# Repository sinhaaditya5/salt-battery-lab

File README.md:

<div align="center">

<br>

**A rebuildable engineering and business study of a sodium "salt battery" startup:<br>
from DFT and cell models to CAD, PCB, techno-economics and an honest go/no-go verdict.**

[Quickstart](#quickstart) ·
[Results](#results-at-a-glance) ·
[Gallery](#gallery) ·
[Architecture](#architecture) ·
[Verdict](#the-verdict) ·
[Deliverables](DELIVERABLES) ·
[Release v1.1.0](https://github.com/sinhaaditya5/salt-battery-lab/releases/tag/v1.1.0)

</div>

---

> [!IMPORTANT]
> **This is a pre-prototype study, not a product.** No cell has been built, so nothing here is measured.
> Every number carries an evidence tag (`[LIT]`, `[VENDOR]`, `[CALC]`, `[SIM]`, `[ASSUMPTION]`, `[TARGET]`) that
> resolves in [`CLAIMS_LEDGER.csv`](CLAIMS_LEDGER.csv). The designs are concepts, **not for fabrication**.
> See the [claims boundary](#claims-boundary).

## Overview

**Salt Battery Lab** answers two startup briefs with one parameter set, one claims ledger and one rebuild script:

| | What it is | Highlights |
|---|---|---|
| 💧 **[Aqueous track](DELIVERABLES)** · `sim/s01…s10` | **R0/R1**: a water-based sodium-ion battery as *"the battery you're allowed to put indoors"* for data-centre and telecom UPS in India. The study runs from a kit re-run to PyBaMM validation, an R1 DFN with Monte Carlo, gas and water budgets, a uMLIP + DFT+U screen, build-up, thermal/abuse, TEA and market sizing. | 10 simulations · 164 logged sources · 28-slide deck · report · YC W27 application · **no-go memo** |
| 🧂 **[Project Salt](PROJECT_SALT)** · `sim/s11…s16` | **Salt-derived chemistries** tested against 360 Wh/kg, a 5-minute charge for 1,500 km, $3 and non-flammability. Includes a 30-architecture feasibility matrix, DFT+U on Na/NaCl/Cl₂/Fe-Co-Ni chlorides, a salt-iron cell model, factory scenarios, the S-cell R0, the SCM-1 board and firmware, and the P1 / SM-48T / SC-UPS-1 designs. | QE 7.6 on AWS spot · STEP + CADCraft drawings · KiCad 10 · 19/19 firmware tests · **Outcome B** |

<div align="center">

<br><sub><b>SM-48T</b>: 48 V telecom/edge backup module concept (7U, 19-inch) built from P1 planar salt-iron cells. Blender render of the build123d CAD model.</sub>
</div>

## Results at a glance

Every number below is regenerated by [`run_all.sh`](run_all.sh) and traces to a claim in [`CLAIMS_LEDGER.csv`](CLAIMS_LEDGER.csv)
or [`PROJECT_SALT/00_START_HERE/CLAIMS_LEDGER.csv`](PROJECT_SALT/00_START_HERE/CLAIMS_LEDGER.csv).

| ID | Area | Test | Result | Status |
|:--:|---|---|---|:--:|
| T1 | Software | pytest suites on the EC2 build host | 80 collected: 78 passed, 2 skipped, 0 failed | ✅ pass |
| T2 | Reproducibility | S1 re-run of the R0 kit scripts vs the kit's expected outputs | 9 / 9 match `[C-101]` | ✅ pass |
| T3 | Cell model | S2 PyBaMM sodium DFN vs published curves (gate: MAE ≤ 60 mV) | misses by **67–121 mV** `[SIM; C-102]` | ❌ fail, documented |
| T4 | Atomistic | S5 uMLIP voltages and birnessite interlayer vs literature | voltage MAE 0.33 V (0.7 V errors for NTP and Prussian white); interlayer 7.16 Å vs 7.19 Å XRD `[SIM; C-110, C-111]` | 🔶 finding |
| T5 | DFT | S11 PBE conversion voltages, 2 Na + MCl₂ → 2 NaCl + M | Fe 2.60 V, Ni 2.85 V vs 2.49, 2.68 V experiment; Fe/Co/Ni errors +0.11 to +0.27 V at U = 0 `[SIMULATED]` | ✅ pass |
| T6 | Cell design | S7 R1 12 V block energy density | **17.6 Wh/kg** (13.7–22.1), Aquion-class `[CALC; C-115]` | 🔶 finding |
| T7 | Thermal | S8 temperature rise in a 15-min UPS discharge | 2.8 K `[SIM; C-119]` | ✅ pass |
| T8 | Cost | S9 R1 cost vs LFP pack price | **~$350/kWh** `[CALC; C-122]` vs $70/kWh `[LIT; C-005]` | 🔶 finding |
| T9 | TCO | S9 15-year cost per kWh of 15-min UPS backup | R1 $1,228 · LFP $720 · VRLA $990 `[CALC; C-123]` | 🔶 finding |
| T10 | Energy | S12 best salt-derived cell (N08) vs the 360 Wh/kg target | P50 **259**, P90 292 Wh/kg `[CALCULATED]` | ❌ target missed |
| T11 | Charging | S13 5-min charge for 1,500 km | needs **3.8 MW** (11.7C) vs the 3.75 MW MCS ceiling `[CALCULATED]` | ❌ target missed |
| T12 | Cost floor | S12/S13 $3 target, six readings | inactive parts alone exceed $3/kWh; cell floors $41–152/kWh `[CALCULATED]` | ❌ target missed |
| T13 | Salt-iron cell | S14 5-min charge of the Na–FeCl₂ cell | 0.8–4.3 V overpotential drives it past the 3.05 V overcharge reaction `[SIMULATED]` | ❌ target missed |
| T14 | Factory | S15 1 GWh/yr India, salt-iron vs NFPP | ~$380/kWh vs ~$83/kWh `[CALCULATED]` | 🔶 finding |
| T15 | Electronics | SCM-1 ERC and firmware host tests | ERC 0 · 19 / 19 tests; layout is a draft (37 unrouted nets) | 🔁 in progress |
| T16 | Documents | Claims linter over the deck, report and one-pager | 0 problems | ✅ pass |

<sub>✅ pass · ❌ fails a founder target or a validation gate, recorded rather than hidden · 🔶 finding that reshapes the plan · 🔁 in progress</sub>

**What the simulations changed:** energy density sets the cost. The R1 block lands at 17.6 Wh/kg, where Aquion sat before it failed, and at ~$350/kWh, so the aqueous *factory* company is a **no-go** (T6, T8). Fire codes don't hand the advantage to aqueous sodium either: an unlisted chemistry gets 3 kWh under IFC 2024, against lithium's 20 kWh `[LIT; C-007, C-008]`.

Project Salt showed the founder targets conflict with physics and economics (T10–T13). **The salt is almost free; the battery is not.** The one testable lever is a ≤ 0.5 mm β''-alumina separator with a ≥ 75 mAh/cm² salt-iron cathode `[CALCULATED]`. The S-cell R0 build package exists to test exactly that, after a near-free buyer test.

## Gallery

### Devices

| R1 12 V monobloc | R1 exploded, annotated | R1 UPS cabinet in a data-centre room |
|:--:|:--:|:--:|
|  |  |  |
| **SM-48T 48 V module** | **SM-48T cutaway** | **SC-UPS-1 cabinet, open** |
|  |  |  |
| **P1 planar salt-iron cell, exploded** | **S-cell R0 test cell** | **SCM-1 salt-cell test monitor** (draft layout) |
|  |  |  |

<div align="center">

<br><sub><b>SB-GA-001</b>: R1 12 V monobloc general arrangement (front, top and side views, section A-A, vent detail B) at 1:2 on A2, generated headlessly in CADCraft (<a href="drawings/out/SB-GA-001.pdf">PDF</a> · <a href="drawings/out/SB-GA-001.dxf">DXF</a>). Concept only.</sub>
</div>

<details>
<summary><b>More drawings:</b> SB-SM-001 (SM-48T module)</summary>

Also in [`drawings/out`](drawings/out):
- SB-GA-002: R1 cell and electrode stack
- SB-GA-003: R1 UPS cabinet
- SB-SC-001: S-cell R0
- SB-TM-001: module thermal management
- SB-UPS-001: SC-UPS-1

</details>

### Simulations

| Chemistry matrix: Pareto front (S12) | Energy ladder vs the 360 Wh/kg target (S12) |
|:--:|:--:|
|  |  |
| **DFT+U: conversion voltage vs U (S11)** | **DFT+U: projected density of states (S11)** |
|  |  |
| **Fast charge: validated Li-ion DFN benchmark (S13a)** | **Six readings of the $3 target (S13b)** |
|  |  |
| **Salt-iron cell model (S14)** | **Factory cost and tornado (S15)** |
|  |  |
| **uMLIP voltage parity (S5)** | **R1 rate retention vs electrode loading (S3)** |
|  |  |
| **R1 cost waterfall (S9)** | **15-year UPS TCO: R1 vs LFP vs VRLA (S9)** |
|  |  |

<details>
<summary><b>More charts:</b> PyBaMM validation, water window, thermal, build-up, market</summary>

| PyBaMM validation, documented failure (S2) | Water stability window (S4) |
|:--:|:--:|
|  |  |
| **R1 temperature in a 15-min UPS discharge (S8)** | **SM-48T module thermal budget (S16)** |
|  |  |
| **Energy density vs benchmarks (S7)** | **India UPS market, TAM / SAM / SOM (S10)** |
|  |  |

Every chart also exists as a 300 dpi PNG and an SVG, with a `.caption.txt` file that carries its claim tags ([`DELIVERABLES/7_simulation_charts`](DELIVERABLES/7_simulation_charts)).

</details>

### System design

| System architecture | Salt-iron cell electrochemistry |
|:--:|:--:|
|  |  |
| **SM-48T module electrical** | **Safety comparison** |
|  |  |
| **Validation ladder (aqueous)** | **Gate ladder G1–G5 (S-cell)** |
|  |  |

<details>
<summary><b>Roadmap and unit economics</b></summary>

</details>

## Architecture

Every tagged value flows from **one package**, [`params/`](params): `product_params.py` holds the tagged values and `design.py` derives geometry, mass and energy from them. The CAD, the drawings, the firmware limits, the spreadsheets and every simulation therefore describe the same product. Every claim in a document resolves to the ledger.

```mermaid
flowchart LR
    P["params/*.py<br/><i>single source of truth</i>"]
    L["CLAIMS_LEDGER.csv<br/><i>every number → evidence</i>"]
    R["research/<br/>sources.csv · notes"]

    subgraph SIM [Simulations]
        A[s05 uMLIP · s06/s11 DFT+U<br/>QE 7.6 on EC2 spot]
        C[s02 PyBaMM · s03 DFN+MC<br/>s04 gas · s08/s16 thermal · s14 S-cell]
        E[s07 build-up · s09 TEA · s10 market<br/>s12 matrix · s13 targets · s15 factory]
    end
    subgraph GEO [Geometry and hardware]
        CAD[cad/ build123d → STEP/STL/GLB]
        DWG[drawings/ CADCraft → DXF/PDF]
        PCB[pcb/ KiCad + firmware limits.h]
    end
    subgraph OUT [Communication]
        RND[renders/ Blender]
        DOC[docs/ deck · report · one-pager]
        FIN[finance/ live-formula xlsx]
        VID[video/ narrated explainer]
    end
    T["tests/ + docs/lint.py"]
    PK["DELIVERABLES/ · PROJECT_SALT/"]

    P --> SIM
    P --> CAD --> RND
    P --> DWG
    P --> PCB
    R --> L
    SIM --> L
    SIM --> FIN
    L --> DOC
    SIM & CAD & PCB & DOC & FIN & VID --> PK
    T -. gates .-> P & SIM & CAD & DOC
```

More detail in [`docs/ARCHITECTURE.md`](docs/ARCHITECTURE.md).

## Quickstart

```bash
git clone https://github.com/sinhaaditya5/salt-battery-lab.git
cd salt-battery-lab

make setup          # Python 3.12 venv + pinned CI requirements
make link           # expose the clone at the lab path the scripts expect
make check          # integrity gate: secrets, file sizes, JSON/CSV/Python validity
make test           # params · sim models · DFT · docs lint · Project Salt suites
make firmware-test  # SCM-1 firmware host unit tests (C11, -Werror)
```

Use the parameter set directly:

```python
from params.product_params import MONOBLOC, R0, ALLOWED_TAGS   # tagged values
import params.design as D                                      # derived geometry, mass, energy
from params.scell_params import OPERATE                        # S-cell operating window → firmware limits
```

### Full pipeline

`./run_all.sh` rebuilds every artefact in dependency order and never launches cloud machines. Stages beyond the models need external tools:

| Stage | Command | Requires |
|---|---|---|
| Integrity, tests | `make check` · `make test` · `make firmware-test` | Python 3.12, a C compiler |
| Models (S1–S16) | `./run_all.sh --fast` | `tools/ec2_build/requirements.txt` (PyBaMM, MACE, CHGNet, pymatgen, ASE) |
| ML potentials | `scripts/fetch_assets.sh models` | MACE-MP-0 / 0b3 weights (SHA-256 pinned) |
| CAD | `python cad/make_cad.py` · `make_scell.py` · `make_smodule.py` | build123d (OpenCascade) |
| Drawings | `python drawings/make_drawings.py` | CADCraft `cadcraft-cli` |
| Renders | `python renders/run_renders.py` · `run_salt_renders.py` | Blender 5.0.1 |
| PCB | `pcb/build_scm.sh` | KiCad 10 (`kicad-cli`); Freerouting optional |
| Spreadsheets, docs | `python finance/make_*.py` · `python docs/make_*.py` | LibreOffice (recalculation check) |
| MATLAB stems | `python tools/matlab/make_stem.py --run` | GNU Octave |
| Video | `python video/make_video.py` | ffmpeg, macOS `say` |
| README imagery | `make assets` | Pillow, ffmpeg |
| DFT (opt-in, costs money) | `sim/s06_dft_ec2/launch.sh` → `sim/s11_dft_chlorides/ec2/ec2_s11.sh` | AWS account, QE 7.6, founder approval |

Step-by-step instructions are in [`docs/REPRODUCIBILITY.md`](docs/REPRODUCIBILITY.md). Heavy builds ran on an x86 spot build host ([`tools/ec2_build/`](tools/ec2_build)).

## The verdict

Each version added one layer to the study:

| Version | Layer | Key documents |
|---|---|---|
| v0.1 | Lab layout, verified R0 kit (50/50 SHA-256), S1 kit re-run, S5 uMLIP relax, S6 DFT+U package, params v0 | [R0 kit](00_source_kit/Salt_Battery_R0_Reference_Cell_Kit_v1/START_HERE.md) · [S6](sim/s06_dft_ec2/README.md) |
| v0.2 | S2–S4 and S8 cell models; R1 design; 164 sources; S9 TEA; S7 build-up; S10 market; IDEA v2 with kill criteria | [IDEA v2](decisions/IDEA_v2.md) · [research notes](research/RESEARCH_NOTES.md) |
| v0.3 | Diagrams, claims ledger, decision memo, test suites, claims linter, financial model, 28-slide deck | [decision memo](DELIVERABLES/STARTUP_DECISION_MEMO.md) · [red team](decisions/RED_TEAM.md) |
| v0.4 | Report, one-pager, data room, `run_all.sh`, narrated explainer video, YC answers v3 | [data room](DELIVERABLES/10_data_room/Data_Room_Index.md) · [YC](DELIVERABLES/0_YC_APPLICATION) |
| v1.0 | Project Salt: 30-architecture matrix, founder targets, S-cell R0, SCM-1, DFT+U on chlorides | [executive verdict](PROJECT_SALT/00_START_HERE/EXECUTIVE_VERDICT.md) |
| v1.1 | S11 completed on EC2; P1 cell, SM-48T module, SC-UPS-1 cabinet; renders, drawings, spreadsheet, full record | [DFT results](PROJECT_SALT/02_COMPUTATIONAL_CHEMISTRY/dft_u/RESULTS.md) · [release notes](PROJECT_SALT/13_RELEASE/version_history/CHANGELOG.md) |

**Aqueous track:**
- **No-go** on a water-based sodium battery *manufacturing* company today.
- **Go-with-conditions** on a 12-week falsification sprint (≤ ₹10 lakh `[ASSUMPTION]`). It starts with a near-free buyer test, with discovery for the better-placed wedge (battery fire-code / hazard-analysis software) running alongside.

**Project Salt: Outcome B.**
- No salt-derived chemistry meets the combined specification.
- The closest candidates are N08 anode-free Na solid-state (energy), S03 salt-iron (salt as the active material) and N02 NFPP Na-ion (balance). None of them wins.

Full details: [`STARTUP_DECISION_MEMO.md`](DELIVERABLES/STARTUP_DECISION_MEMO.md) · [`EXECUTIVE_VERDICT.md`](PROJECT_SALT/00_START_HERE/EXECUTIVE_VERDICT.md) · [known limitations](PROJECT_SALT/13_RELEASE/known_limitations.md) · [original lab notebook](docs/LAB_NOTEBOOK.md).

## Repository layout

```text
salt-battery-lab/
├── params/                     # single source of truth: tagged values → derived design
├── sim/                        # one folder per stage: README · code · out/
│   ├── s01…s10/                #   aqueous track: kit re-run → PyBaMM → DFN → gas → atomistic → TEA → market
│   ├── s06_dft_ec2/            #   DFT+U package and runs on AWS Graviton spot
│   ├── s11_dft_chlorides/      #   Na / NaCl / Cl2 / Fe-Co-Ni chloride DFT+U campaign
│   └── s12…s16/                #   Project Salt: matrix, targets, S-cell, factory, module thermal
├── cad/  drawings/  renders/   # build123d models, CADCraft drawings, Blender scenes
├── pcb/                        # KiCad generators, BMS monitor, SCM-1 board + firmware
├── diagrams/  finance/  docs/  video/   # charts, live-formula xlsx, deck/report generators, explainer
├── research/  decisions/       # 164 sources, notes, competitors, grants; IDEA v2, red team
├── tests/                      # pytest suites (params · models · CAD · DFT · docs lint · Project Salt)
├── tools/                      # env, plot style, EC2 build host, package assembly, pseudopotentials
├── DELIVERABLES/               # investor docs, CAD, charts, data room, YC application
├── PROJECT_SALT/               # 14-section package; start at 00_START_HERE/
├── 00_source_kit/              # read-only R0 reference-cell kit (SHA-256 verified)
├── scripts/                    # integrity gate, asset fetcher, README imagery
├── .github/                    # CI, templates, Dependabot
├── CLAIMS_LEDGER.csv           # evidence register for every number
├── run_all.sh                  # rebuild everything
└── Makefile                    # entry points: setup · check · test · assets · rebuild
```

## Open questions

The study's most valuable output is a precise list of what remains unknown:

1. **Buyer test (K4).** Do Indian data-centre or telecom buyers face a lithium-indoor premium or prohibition of ≥ $150–250/kWh? This applies whatever the chemistry.
2. **Aqueous cell.** Can a perchlorate-free cell reach ≥ 30 Wh/kg at block level with ≥ 99.88 % coulombic efficiency at 40 mg/cm²?
3. **Thick salt-iron cathodes.** Do cathodes of ≥ 75–100 mAh/cm² stay usable at 190 °C (gates G2 and G4 of the S-cell R0 campaign)?
4. **Ceramic cost.** Can β''-alumina reach ≤ $15/kg in ≤ 0.5 mm, large-area form?
5. **Factory capex.** Is a molten-salt cell line possible at ≤ ~$100 per kWh/yr, about 7× below the only published anchor?
6. **Model validation.** Why does the shipped PyBaMM sodium DFN miss the published curves by 67–121 mV?

Limitations are listed in [`PROJECT_SALT/13_RELEASE/known_limitations.md`](PROJECT_SALT/13_RELEASE/known_limitations.md).

## Claims boundary

| We have shown | We do **not** claim |
|---|---|
| A reproducible, evidence-tagged study: 80 tests, a claims linter, every number in a ledger | Any measured cell performance. No cell exists |
| Simulations that reject targets on physics and economics before money is spent | That any chemistry here is investable or novel. Every architecture has close prior art |
| Concept CAD, drawings, a KiCad board and firmware derived from one parameter set | That the designs are ready to fabricate. SCM-1 is a draft layout |
| A testable cost lever (thin β''-alumina + thick cathode) and the build package to test it | That the lever works: it is the hypothesis for the S-cell R0 campaign |

## Contributing

Corrections to sources and claims are the most valuable contribution. Please read [`CONTRIBUTING.md`](CONTRIBUTING.md) and the
[Code of Conduct](CODE_OF_CONDUCT.md), and use the **Claim correction** issue template. Run `make check` and `make test` before opening a pull request. Security issues: see [`SECURITY.md`](SECURITY.md).

## Citation

To reference this work, cite it via [`CITATION.cff`](CITATION.cff)
(GitHub shows a **Cite this repository** button in the sidebar).

## License

Copyright © 2026 Aditya. **All rights reserved.** The repository is public for review and reference, and no licence to reuse it is granted. See [`LICENSE`](LICENSE). Third-party components (GBRV pseudopotentials, MACE-MP weights, Freerouting) and the tools used by the pipeline (Quantum ESPRESSO, Blender, KiCad, CADCraft, build123d/OpenCascade, PyBaMM, LibreOffice, Octave) keep their own licences. See [`THIRD_PARTY_NOTICES.md`](THIRD_PARTY_NOTICES.md).

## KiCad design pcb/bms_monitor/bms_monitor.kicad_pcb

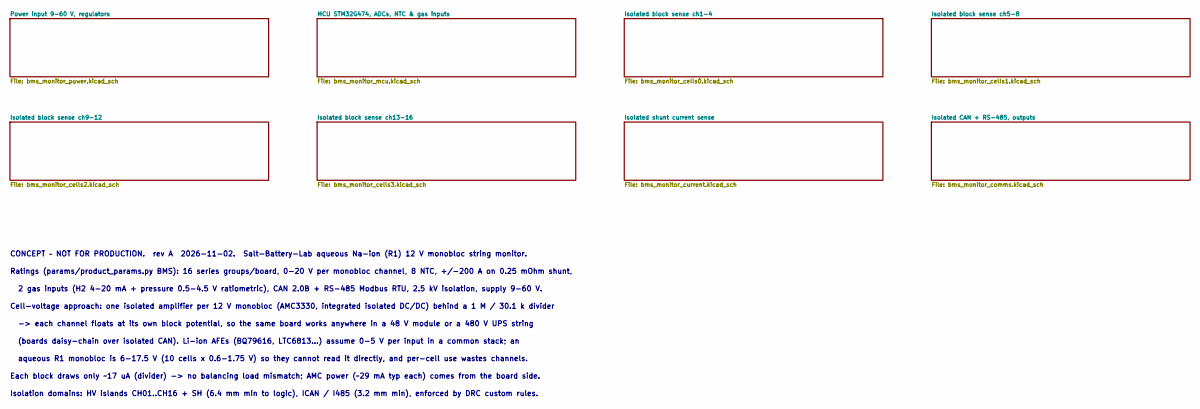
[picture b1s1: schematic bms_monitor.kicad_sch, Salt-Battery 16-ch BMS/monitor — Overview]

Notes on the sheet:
CONCEPT – NOT FOR PRODUCTION. rev A 2026-11-02. Salt-Battery-Lab aqueous Na-ion (R1) 12 V monobloc string monitor.
Ratings (params/product_params.py BMS): 16 series groups/board, 0-20 V per monobloc channel, 8 NTC, +/-200 A on 0.25 mOhm shunt,
2 gas inputs (H2 4-20 mA + pressure 0.5-4.5 V ratiometric), CAN 2.0B + RS-485 Modbus RTU, 2.5 kV isolation, supply 9-60 V.
Cell-voltage approach: one isolated amplifier per 12 V monobloc (AMC3330, integrated isolated DC/DC) behind a 1 M / 30.1 k divider
-> each channel floats at its own block potential, so the same board works anywhere in a 48 V module or a 480 V UPS string
(boards daisy-chain over isolated CAN). Li-ion AFEs (BQ79616, LTC6813...) assume 0-5 V per input in a common stack; an
aqueous R1 monobloc is 6-17.5 V (10 cells x 0.6-1.75 V) so they cannot read it directly, and per-cell use wastes channels.
Each block draws only ~17 uA (divider) -> no balancing load mismatch; AMC power (~29 mA typ each) comes from the board side.
Isolation domains: HV islands CH01..CH16 + SH (6.4 mm min to logic), ICAN / I485 (3.2 mm min), enforced by DRC custom rules.

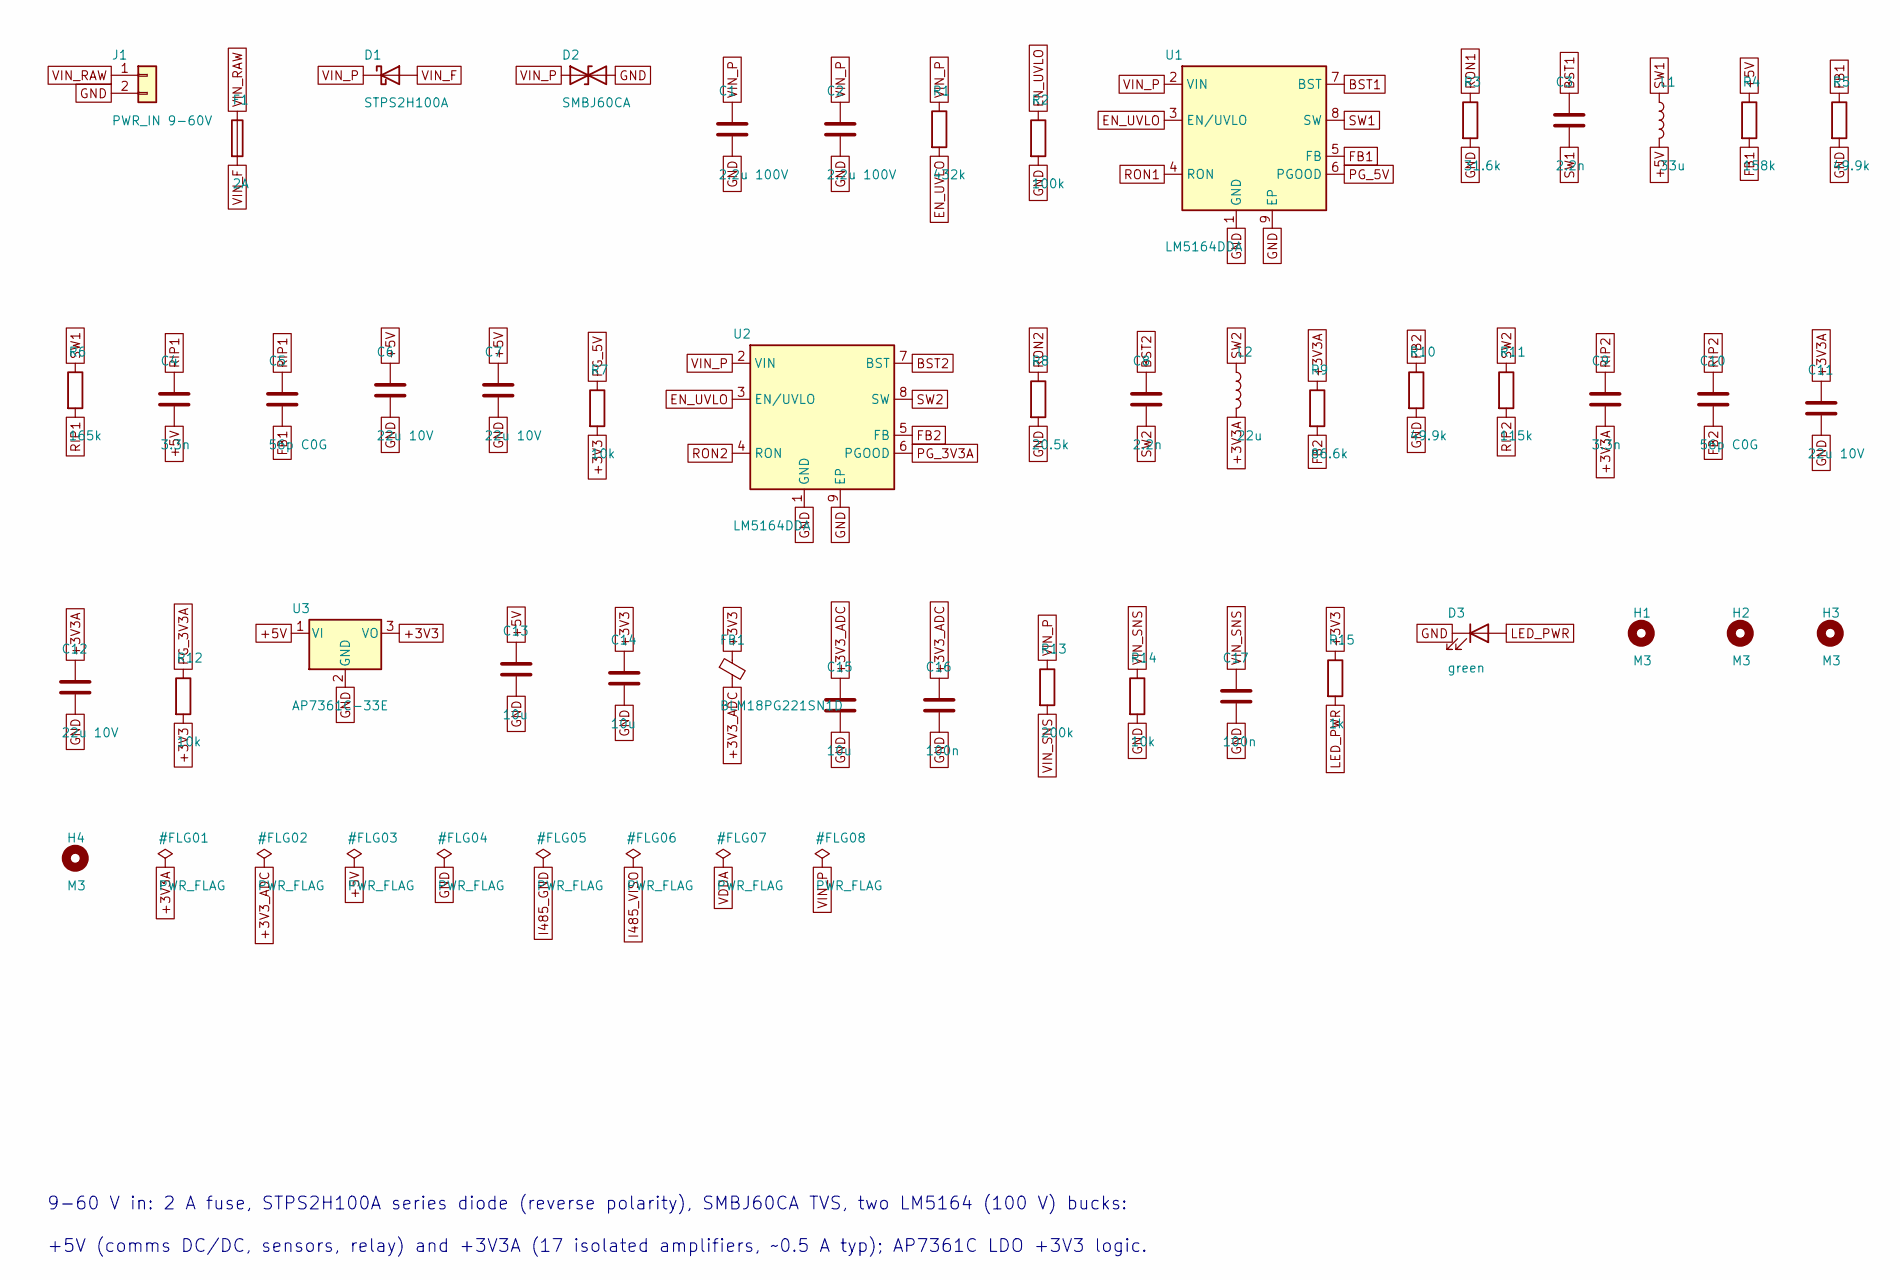
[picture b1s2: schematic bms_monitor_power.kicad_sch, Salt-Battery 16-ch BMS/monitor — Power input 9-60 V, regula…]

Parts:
C1, C2: 2.2u 100V; C_1210_3225Metric
C3, C8: 2.2n; C_0603_1608Metric
C4, C9: 3.3n; C_0603_1608Metric
C5, C10: 56p C0G; C_0603_1608Metric
C6, C7, C11, C12: 22u 10V; C_1206_3216Metric
C13, C14, C15: 10u; C_0805_2012Metric
C16, C17: 100n; C_0603_1608Metric
D1: STPS2H100A; D_SMA; MPN STPS2H100A
D2: SMBJ60CA; D_SMB; MPN SMBJ60CA
D3: green; LED_0603_1608Metric
F1: 2A; Fuse_Littelfuse-NANO2-451_453; MPN 0451002.MRL
FB1: BLM18PG221SN1D; L_0603_1608Metric; MPN BLM18PG221SN1D
H1, H2, H3, H4: M3; MountingHole_3.2mm_M3
J1: PWR_IN 9-60V; TerminalBlock_Phoenix_MKDS-1,5-2-5.08_1x02_P5.08mm_Horizont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; MPN 1715721
L1: 33u; L_Bourns_SRN6045TA; MPN SRN6045TA-330M
L2: 22u; L_Bourns_SRN6045TA; MPN SRN6045TA-220M
R1: 432k; R_0603_1608Metric
R2: 100k; R_0603_1608Metric
R3: 31.6k; R_0603_1608Metric
R4: 158k; R_0603_1608Metric
R5, R10: 49.9k; R_0603_1608Metric
R6: 165k; R_0603_1608Metric
R7, R12, R14: 10k; R_0603_1608Metric
R8: 20.5k; R_0603_1608Metric
R9: 86.6k; R_0603_1608Metric
R11: 115k; R_0603_1608Metric
R13: 200k; R_0603_1608Metric
R15: 1k; R_0603_1608Metric
U1, U2: LM5164DDA; HSOP-8-1EP_3.9x4.9mm_P1.27mm_EP2.41x3.1mm_ThermalVias; MPN LM5164DDAR
U3: AP7361C-33E; SOT-223-3_TabPin2; MPN AP7361C-33E-13

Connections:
+3V3: C14.1, FB1.1, R7.2, R12.2, R15.1, U3.3 (VO); also elsewhere on the board
+3V3A: C9.2, C11.1, C12.1, L2.2, R9.1; also elsewhere on the board
+3V3_ADC: C15.1, C16.1, FB1.2; also elsewhere on the board
+5V: C4.2, C6.1, C7.1, C13.1, L1.2, R4.1, U3.1 (VI); also elsewhere on the board
BST1: C3.1, U1.7 (BST)
BST2: C8.1, U2.7 (BST)
EN_UVLO: R1.2, R2.1, U1.3 (EN/UVLO), U2.3 (EN/UVLO)
FB1: C5.2, R4.2, R5.1, U1.5 (FB)
FB2: C10.2, R9.2, R10.1, U2.5 (FB)
GND: C1.2, C2.2, C6.2, C7.2, C11.2, C12.2, C13.2, C14.2, C15.2, C16.2, C17.2, D2.2 (A2), D3.1 (K), J1.2, R2.2, R3.2, R5.2, R8.2, R10.2, R14.2, U1.1 (GND), U1.9 (EP), U2.1 (GND), U2.9 (EP), U3.2 (GND); also elsewhere on the board
LED_PWR: D3.2 (A), R15.2
PG_3V3A: R12.1, U2.6 (PGOOD); also elsewhere on the board
PG_5V: R7.1, U1.6 (PGOOD); also elsewhere on the board
RIP1: C4.1, C5.1, R6.2
RIP2: C9.1, C10.1, R11.2
RON1: R3.1, U1.4 (RON)
RON2: R8.1, U2.4 (RON)
SW1: C3.2, L1.1, R6.1, U1.8 (SW)
SW2: C8.2, L2.1, R11.1, U2.8 (SW)
VIN_F: D1.2 (A), F1.2
VIN_P: C1.1, C2.1, D1.1 (K), D2.1 (A1), R1.1, R13.1, U1.2 (VIN), U2.2 (VIN); also elsewhere on the board
VIN_RAW: F1.1, J1.1
VIN_SNS: C17.1, R13.2, R14.1; also elsewhere on the board

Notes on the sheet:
9-60 V in: 2 A fuse, STPS2H100A series diode (reverse polarity), SMBJ60CA TVS, two LM5164 (100 V) bucks:
+5V (comms DC/DC, sensors, relay) and +3V3A (17 isolated amplifiers, ~0.5 A typ); AP7361C LDO +3V3 logic.

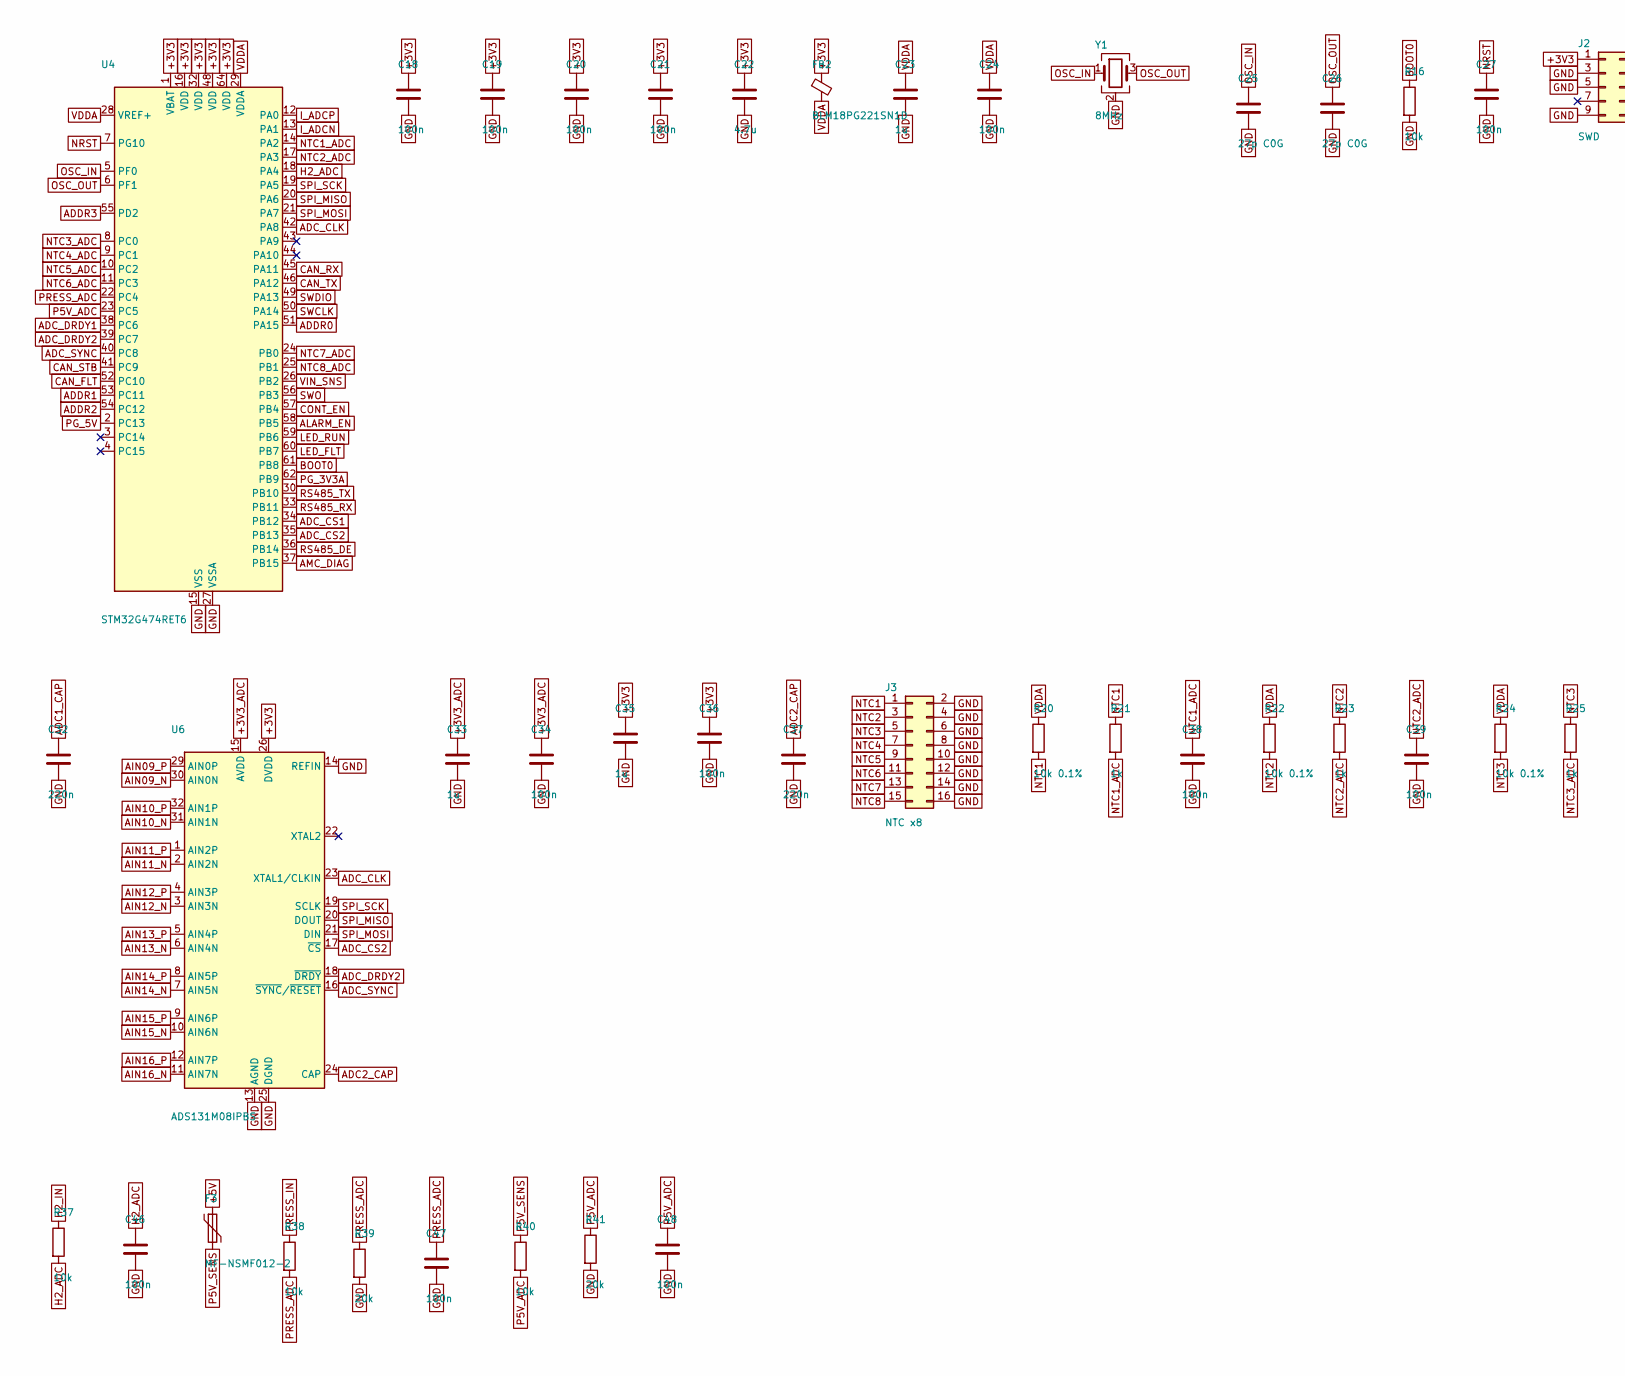
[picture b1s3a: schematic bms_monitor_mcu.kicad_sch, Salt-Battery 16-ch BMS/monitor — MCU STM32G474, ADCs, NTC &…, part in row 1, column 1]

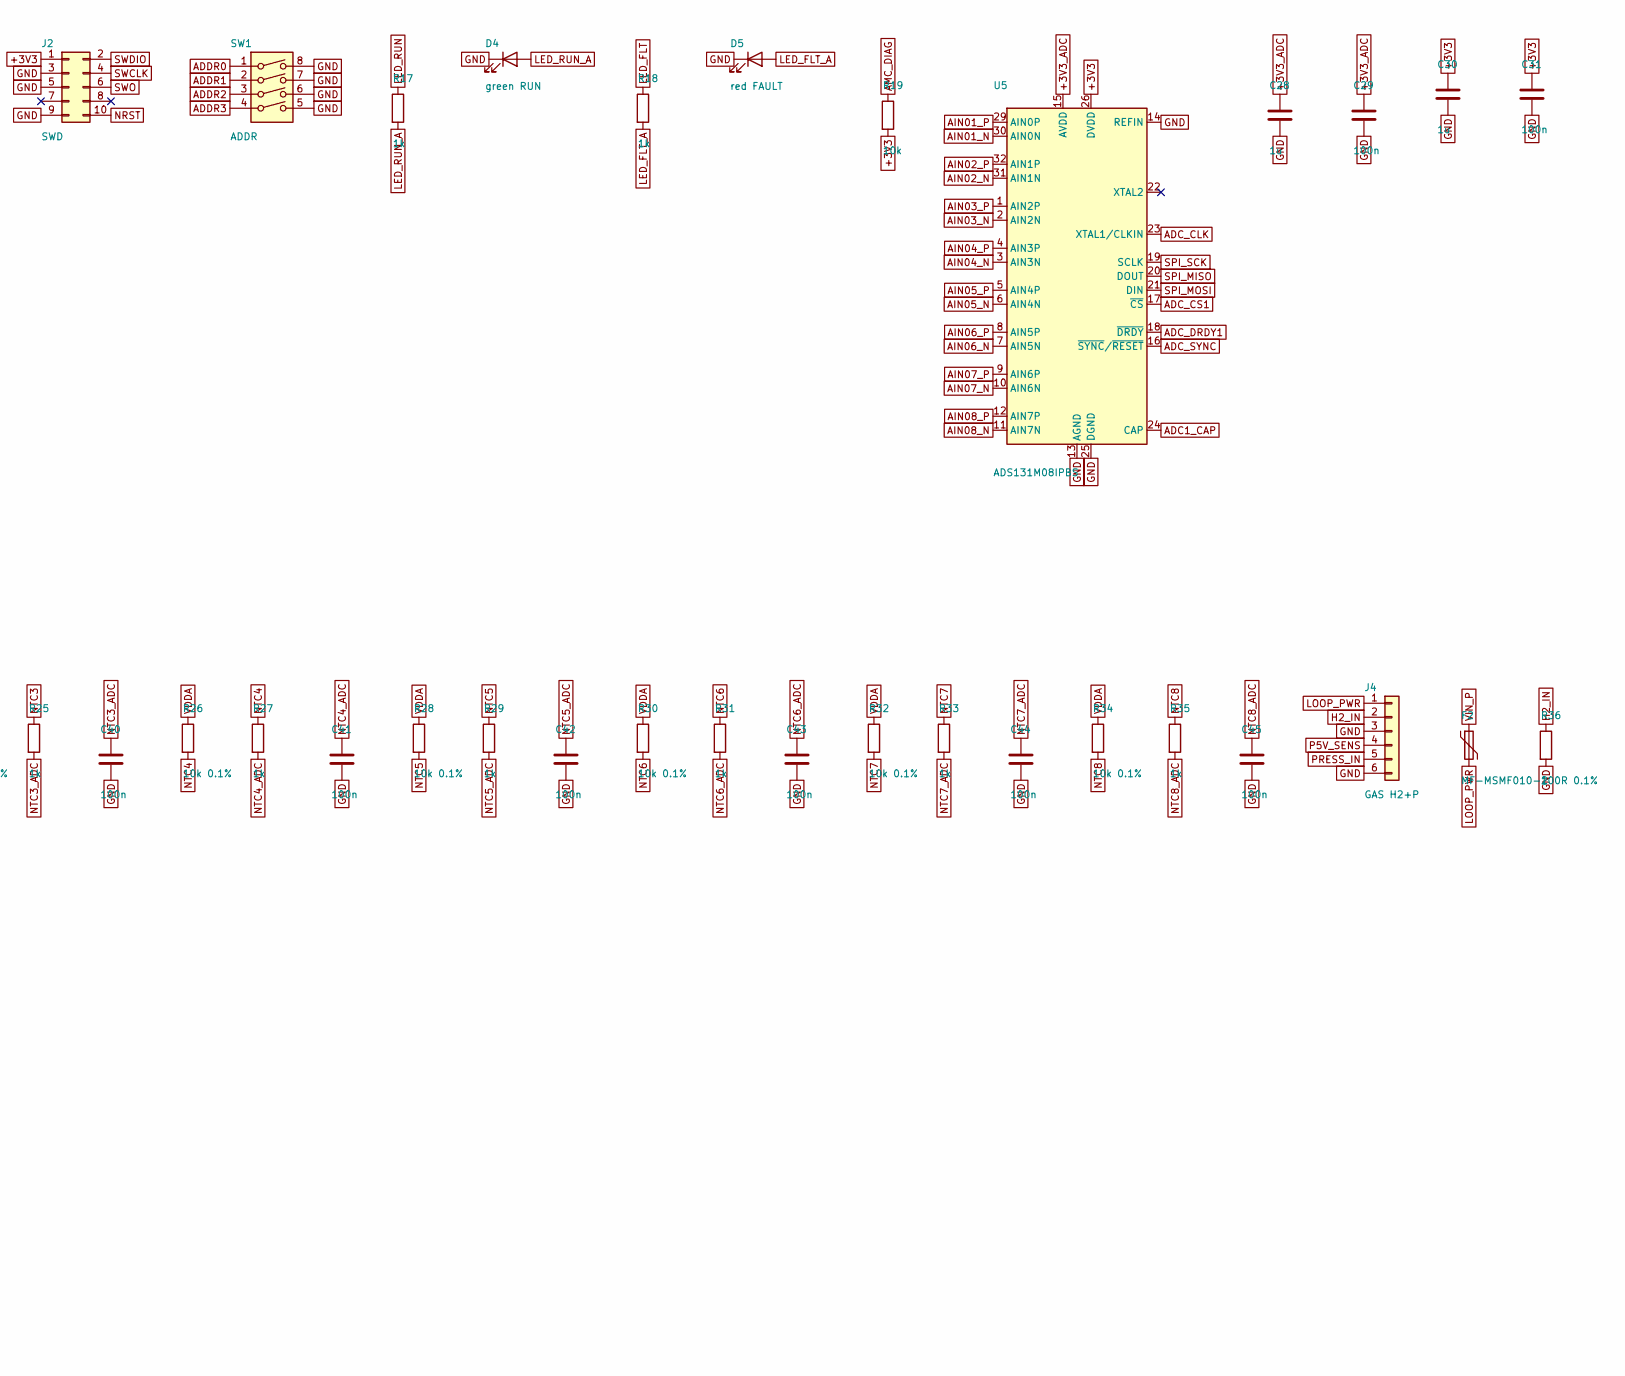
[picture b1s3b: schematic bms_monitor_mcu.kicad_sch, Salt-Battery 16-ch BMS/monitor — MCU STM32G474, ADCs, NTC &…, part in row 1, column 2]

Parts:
C18, C19, C20, C21, C24, C27, C29, C31, C34, C36, C38, C39, C40, C41, C42, C43, C44, C45, C46, C47, C48: 100n; C_0603_1608Metric
C22: 4.7u; C_0805_2012Metric
C23, C28, C30, C33, C35: 1u; C_0603_1608Metric
C25, C26: 27p C0G; C_0603_1608Metric
C32, C37: 220n; C_0603_1608Metric
D4: green RUN; LED_0603_1608Metric
D5: red FAULT; LED_0603_1608Metric
F2: MF-MSMF010-2; Fuse_1812_4532Metric; MPN MF-MSMF010-2
F3: MF-NSMF012-2; Fuse_1206_3216Metric; MPN MF-NSMF012-2
FB2: BLM18PG221SN1D; L_0603_1608Metric; MPN BLM18PG221SN1D
J2: SWD; PinHeader_2x05_P1.27mm_Vertical_SMD
J3: NTC x8; IDC-Header_2x08_P2.54mm_Vertical
J4: GAS H2+P; PhoenixContact_MC_1,5_6-G-3.5_1x06_P3.50mm_Horizontal; MPN 1803316
R16, R19, R37, R38, R40: 10k; R_0603_1608Metric
R17, R18, R21, R23, R25, R27, R29, R31, R33, R35: 1k; R_0603_1608Metric
R20, R22, R24, R26, R28, R30, R32, R34: 10k 0.1%; R_0603_1608Metric
R36: 100R 0.1%; R_1206_3216Metric
R39, R41: 20k; R_0603_1608Metric
SW1: ADDR; SW_DIP_SPSTx04_Slide_6.7x11.72mm_W8.61mm_P2.54mm_LowProfile
U4: STM32G474RET6; LQFP-64_10x10mm_P0.5mm; MPN STM32G474RET6
U5, U6: ADS131M08IPBS; TQFP-32_5x5mm_P0.5mm; MPN ADS131M08IPBSR
Y1: 8MHz; Crystal_SMD_3225-4Pin_3.2x2.5mm; MPN ABM8-8.000MHZ-B2-T

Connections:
+3V3: C18.1, C19.1, C20.1, C21.1, C22.1, C30.1, C31.1, C35.1, C36.1, FB2.1, J2.1, R19.2, U4.1 (VBAT), U4.16 (VDD), U4.32 (VDD), U4.48 (VDD), U4.64 (VDD), U5.26 (DVDD), U6.26 (DVDD); also elsewhere on the board
+3V3_ADC: C28.1, C29.1, C33.1, C34.1, U5.15 (AVDD), U6.15 (AVDD); also elsewhere on the board
+5V: F3.1; also elsewhere on the board
ADC1_CAP: C32.1, U5.24 (CAP)
ADC2_CAP: C37.1, U6.24 (CAP)
ADC_CLK: U4.42 (PA8), U5.23 (XTAL1/CLKIN), U6.23 (XTAL1/CLKIN)
ADC_CS1: U4.34 (PB12), U5.17 (~CS)
ADC_CS2: U4.35 (PB13), U6.17 (~CS)
ADC_DRDY1: U4.38 (PC6), U5.18 (~DRDY)
ADC_DRDY2: U4.39 (PC7), U6.18 (~DRDY)
ADC_SYNC: U4.40 (PC8), U5.16 (~SYNC/~RESET), U6.16 (~SYNC/~RESET)
ADDR0: SW1.1, U4.51 (PA15)
ADDR1: SW1.2, U4.53 (PC11)
ADDR2: SW1.3, U4.54 (PC12)
ADDR3: SW1.4, U4.55 (PD2)
AIN01_N: U5.30 (AIN0N); also elsewhere on the board
AIN01_P: U5.29 (AIN0P); also elsewhere on the board
AIN02_N: U5.31 (AIN1N); also elsewhere on the board
AIN02_P: U5.32 (AIN1P); also elsewhere on the board
AIN03_N: U5.2 (AIN2N); also elsewhere on the board
AIN03_P: U5.1 (AIN2P); also elsewhere on the board
AIN04_N: U5.3 (AIN3N); also elsewhere on the board
AIN04_P: U5.4 (AIN3P); also elsewhere on the board
AIN05_N: U5.6 (AIN4N); also elsewhere on the board
AIN05_P: U5.5 (AIN4P); also elsewhere on the board
AIN06_N: U5.7 (AIN5N); also elsewhere on the board
AIN06_P: U5.8 (AIN5P); also elsewhere on the board
AIN07_N: U5.10 (AIN6N); also elsewhere on the board
AIN07_P: U5.9 (AIN6P); also elsewhere on the board
AIN08_N: U5.11 (AIN7N); also elsewhere on the board
AIN08_P: U5.12 (AIN7P); also elsewhere on the board
AIN09_N: U6.30 (AIN0N); also elsewhere on the board
AIN09_P: U6.29 (AIN0P); also elsewhere on the board
AIN10_N: U6.31 (AIN1N); also elsewhere on the board
AIN10_P: U6.32 (AIN1P); also elsewhere on the board
AIN11_N: U6.2 (AIN2N); also elsewhere on the board
AIN11_P: U6.1 (AIN2P); also elsewhere on the board
AIN12_N: U6.3 (AIN3N); also elsewhere on the board
AIN12_P: U6.4 (AIN3P); also elsewhere on the board
AIN13_N: U6.6 (AIN4N); also elsewhere on the board
AIN13_P: U6.5 (AIN4P); also elsewhere on the board
AIN14_N: U6.7 (AIN5N); also elsewhere on the board
AIN14_P: U6.8 (AIN5P); also elsewhere on the board
AIN15_N: U6.10 (AIN6N); also elsewhere on the board
AIN15_P: U6.9 (AIN6P); also elsewhere on the board
AIN16_N: U6.11 (AIN7N); also elsewhere on the board
AIN16_P: U6.12 (AIN7P); also elsewhere on the board
ALARM_EN: U4.58 (PB5); also elsewhere on the board
AMC_DIAG: R19.1, U4.37 (PB15); also elsewhere on the board
BOOT0: R16.1, U4.61 (PB8)
CAN_FLT: U4.52 (PC10); also elsewhere on the board
CAN_RX: U4.45 (PA11); also elsewhere on the board
CAN_STB: U4.41 (PC9); also elsewhere on the board
CAN_TX: U4.46 (PA12); also elsewhere on the board
CONT_EN: U4.57 (PB4); also elsewhere on the board
GND: C18.2, C19.2, C20.2, C21.2, C22.2, C23.2, C24.2, C25.2, C26.2, C27.2, C28.2, C29.2, C30.2, C31.2, C32.2, C33.2, C34.2, C35.2, C36.2, C37.2, C38.2, C39.2, C40.2, C41.2, C42.2, C43.2, C44.2, C45.2, C46.2, C47.2, C48.2, D4.1 (K), D5.1 (K), J2.3, J2.5, J2.9, J3.2, J3.4, J3.6, J3.8, J3.10, J3.12, J3.14, J3.16, J4.3, J4.6, R16.2, R36.2, R39.2, R41.2, SW1.5, SW1.6, SW1.7, SW1.8, U4.15 (VSS), U4.27 (VSSA), U4.31 (VSS), U4.47 (VSS), U4.63 (VSS), U5.13 (AGND), U5.14 (REFIN), U5.25 (DGND), U5.27 (AGND), U5.28 (AGND), U6.13 (AGND), U6.14 (REFIN), U6.25 (DGND), U6.27 (AGND), U6.28 (AGND), Y1.2 (G), Y1.4 (G); also elsewhere on the board
H2_ADC: C46.1, R37.2, U4.18 (PA4)
H2_IN: J4.2, R36.1, R37.1
I_ADCN: U4.13 (PA1); also elsewhere on the board
I_ADCP: U4.12 (PA0); also elsewhere on the board
LED_FLT: R18.1, U4.60 (PB7)
LED_FLT_A: D5.2 (A), R18.2
LED_RUN: R17.1, U4.59 (PB6)
LED_RUN_A: D4.2 (A), R17.2
LOOP_PWR: F2.2, J4.1
NRST: C27.1, J2.10, U4.7 (PG10)
NTC1: J3.1, R20.2, R21.1
NTC1_ADC: C38.1, R21.2, U4.14 (PA2)
NTC2: J3.3, R22.2, R23.1
NTC2_ADC: C39.1, R23.2, U4.17 (PA3)
NTC3: J3.5, R24.2, R25.1
NTC3_ADC: C40.1, R25.2, U4.8 (PC0)
NTC4: J3.7, R26.2, R27.1
NTC4_ADC: C41.1, R27.2, U4.9 (PC1)
NTC5: J3.9, R28.2, R29.1
NTC5_ADC: C42.1, R29.2, U4.10 (PC2)
NTC6: J3.11, R30.2, R31.1
NTC6_ADC: C43.1, R31.2, U4.11 (PC3)
NTC7: J3.13, R32.2, R33.1
NTC7_ADC: C44.1, R33.2, U4.24 (PB0)
NTC8: J3.15, R34.2, R35.1
NTC8_ADC: C45.1, R35.2, U4.25 (PB1)
OSC_IN: C25.1, U4.5 (PF0), Y1.1
OSC_OUT: C26.1, U4.6 (PF1), Y1.3
P5V_ADC: C48.1, R40.2, R41.1, U4.23 (PC5)
P5V_SENS: F3.2, J4.4, R40.1
PG_3V3A: U4.62 (PB9); also elsewhere on the board
PG_5V: U4.2 (PC13); also elsewhere on the board
PRESS_ADC: C47.1, R38.2, R39.1, U4.22 (PC4)
PRESS_IN: J4.5, R38.1
RS485_DE: U4.36 (PB14); also elsewhere on the board
RS485_RX: U4.33 (PB11); also elsewhere on the board
RS485_TX: U4.30 (PB10); also elsewhere on the board
SPI_MISO: U4.20 (PA6), U5.20 (DOUT), U6.20 (DOUT)
SPI_MOSI: U4.21 (PA7), U5.21 (DIN), U6.21 (DIN)
SPI_SCK: U4.19 (PA5), U5.19 (SCLK), U6.19 (SCLK)
SWCLK: J2.4, U4.50 (PA14)
SWDIO: J2.2, U4.49 (PA13)
SWO: J2.6, U4.56 (PB3)
VDDA: C23.1, C24.1, FB2.2, R20.1, R22.1, R24.1, R26.1, R28.1, R30.1, R32.1, R34.1, U4.28 (VREF+), U4.29 (VDDA)
VIN_P: F2.1; also elsewhere on the board
VIN_SNS: U4.26 (PB2); also elsewhere on the board

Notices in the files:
README.md:
License: all rights reserved
